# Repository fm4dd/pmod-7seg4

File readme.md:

## 7SEG4 PMOD

### Description

This PMOD provides a multiplexed four-digit 7-segment LED display output to FPGA designs via two double-row PMOD ports (quad-row).
The 7-segment display type "common anode" requires to use inverse logic. With inverse logic, setting the output "LOW" lights up the LED segment. Each digit has its own common anode, but the seven LED segments are shared. To display separate numbers on each digit, the program cycles through each anode with the apropriate segments enabled for this digit.

http://fpga.fm4dd.com/

### Schematic

### PCB Gerber
[7SEG4 PMOD Gerber V1.1](20200130-7seg4-gerber-v11.zip)

### Pin Assignments

#### IceBreaker v1.0

 J1# |  Label | Description   | PMOD1A
-----|--------|---------------|-------
1    |  A     | LED Segment A | 4
2    |  B     | LED Segment B | 2
3    |  C     | LED Segment C | 47
4    |  D     | LED Segment D | 45
7    |  E     | LED Segment E | 3
8    |  F     | LED Segment F | 48
9    |  G     | LED Segment G | 46
10   |  DP    | LED Segment DP| 44

 J2# |  Label | Description      | PMOD1B
-----|--------|------------------|-------
1    |  CA1   | Common AN Digit1 | 43
2    |  CA2   | Common AN Digit2 | 38
3    |  CA3   | Common AN Digit3 | 34
4    |  CA4   | Common AN Digit4 | 31
7    |  -     | Not connected    | 42
8    |  -     | Not connected    | 36
9    |  -     | Not connected    | 32
10   |  CA5   | Common AN Colon  | 28

#### DE0-Nano-SoC

The connection to Intels DE0-Nano-SoC is made through the pmod2nano adapter.

 J1# |  Label | Description    | GPIO0A | GPIO1A
-----|--------|----------------|--------|--------
1    |  E     |  LED Segment E | PIN_W12|PIN_AA15
2    |  F     |  LED Segment F | PIN_Y8 |PIN_AG26
3    |  G     |  LED Segment G | PIN_W8 |PIN_AF23
4    |  *     |  LED Segment DP| PIN_Y5 |PIN_AF21
7    |  A     |  LED Segment A | PIN_AF8|PIN_AH27
8    |  B     |  LED Segment B | PIN_AB4|PIN_AH24
9    |  C     |  LED Segment C | PIN_Y4 |PIN_AE22
10   |  D     |  LED Segment D | PIN_U11|PIN_AG20

 J2# |  Label | Description      | GPIO0B | GPIO1B
-----|--------|------------------|--------|--------
1    |  -     | Not connected    | PIN_AF4| PIN_AH23
2    |  -     | Not connected    | PIN_AF5| PIN_AE19
3    |  -     | Not connected    | PIN_T13| PIN_AD19
4    |  CA5   | Common AN DP     | PIN_AE7| PIN_AE24
7    |  CA1   | Common AN Digit1 | PIN_AG6| PIN_AG23
8    |  CA2   | Common AN Digit2 | PIN_AE4| PIN_AF18
9    |  CA3   | Common AN Digit3 | PIN_T11| PIN_AE20
10   |  CA4   | Common AN Digit4 | PIN_AF6| PIN_AD20

### Example

7SEG4 PMOD, connected to a Icebreaker v1.0 board

#### Verilog

Verilog test program pmod_7seg4_1.v (top-level):
```
// -------------------------------------------------------
// This program is a decimal counter 0..9999, displayed on
// the 4-digit 7-segment display. Counts in 1Hz intervals.
// 12MHz clock: set breakpoint at 23'd5999999 (icebreaker)
// 50MHz clock: set breakpoint at 25'd24999999 (de0-nano)
// -------------------------------------------------------
module pmod_7seg4_1 (
  input clk,
  output seg_a,
  output seg_b,
  output seg_c,
  output seg_d,
  output seg_e,
  output seg_f,
  output seg_g,
  output seg_dp,
  output ca1,
  output ca2,
  output ca3,
  output ca4
);

  reg clk_1hz = 1'b0;
  reg [22:0] clk_count = 23'd0;
  reg [3:0] DIGIT;
  reg [7:0] SEG;
  assign {seg_dp, seg_g, seg_f, seg_e, seg_d, seg_c, seg_b, seg_a} = SEG;
  assign {ca1, ca2, ca3, ca4} = DIGIT;
  reg [3:0] units, tens, hundreds, thousands;

  display_7seg display(.CLK (clk), .units (units), .tens (tens), .hundreds (hundreds), .thousands (thousands), .SEG (SEG), .DIGIT (DIGIT));

  always @(posedge clk)
  begin
    clk_count   <= clk_count + 1;
    if(clk_count == 23'd5999999)
    begin
      clk_count   <= 0;
      clk_1hz <= ~clk_1hz;
    end
  end

  always @(posedge clk_1hz)
  begin
    units <= units + 1;
    if (units == 9)
    begin
      units <= 0;
      tens <= tens + 1;
      if (tens == 9)
      begin
        tens <= 0;
        hundreds <= hundreds + 1;
        if (hundreds == 9)
        begin
          hundreds <= 0;
          thousands <= thousands + 1;
          if(thousands == 9)
          begin
            thousands <= 0;
          end
        end
      end
    end
  end
endmodule // end top-level module

// -------------------------------------------------------
// module display_7seg converts 4 decimal digits to 7-seg
// -------------------------------------------------------
module display_7seg(
  input CLK,
  input [3:0] units, tens, hundreds, thousands,
  output [7:0] SEG,
  output [3:0] DIGIT
);

  reg [3:0] digit_data;
  reg [1:0] digit_posn;
  reg [23:0] prescaler;

  encode_7seg encode(.CLK (CLK), .SEG (SEG), .D (digit_data));

  always @(posedge CLK)
  begin
    prescaler <= prescaler + 24'd1;
    if (prescaler == 24'd50000)     // set 1kHz multiplex frequency
    begin
      prescaler <= 0;               // reset the prescaler to zero
      digit_posn <= digit_posn + 2'd1;
      if (digit_posn == 0)
      begin
        digit_data <= units;       // assign digit_data
        DIGIT <= 4'b1110;          // set the 1 digit pin low (enable)
      end
      if (digit_posn == 2'd1)
      begin
        digit_data <= tens;        // assign digit_data to show tens
        DIGIT <= 4'b1101;          // set the 2 digit pin low (enable)
      end
      if (digit_posn == 2'd2)
      begin
        digit_data <= hundreds;    // assign digit_data to show hundreds
        DIGIT <= 4'b1011;          // set the 3 digit pin low (enable)
      end
      if (digit_posn == 2'd3)
      begin
        digit_data <= thousands;   // assign digit_data to show thousands
        DIGIT <= 4'b0111;          // set the 4 digit pin low (enable)
        digit_posn <= 0;           // reset position counter after 4nd digit
      end
    end
  end
endmodule

// -------------------------------------------------------
// module encode_7seg encodes a bin number as a 7seg digit
// -------------------------------------------------------
module encode_7seg(
  input CLK,
  input [3:0] D,
  output reg [7:0] SEG
);
  
  always @(posedge CLK)
    begin
      case(D)
        //              PGFEDCBA
        4'd0: SEG <= 8'b11000000;
        4'd1: SEG <= 8'b11111001;
        4'd2: SEG <= 8'b10100100;
        4'd3: SEG <= 8'b10110000;
        4'd4: SEG <= 8'b10011001;
        4'd5: SEG <= 8'b10010010;
        4'd6: SEG <= 8'b10000010;
        4'd7: SEG <= 8'b11111000;
        4'd8: SEG <= 8'b10000000;
        4'd9: SEG <= 8'b10010000;
        default: SEG <= 8'b11111111;
      endcase
    end
endmodule
```

#### VHDL

The Verilog example program pmod_7seg4_1.v converted to VHDL as pmod_7seg4_2.vhd:

```
-- -------------------------------------------------------
-- This program is a decimal counter 0..9999, displayed on
-- the 4-digit 7-segment display. Counts in 1Hz intervals.
-- -------------------------------------------------------
library ieee;
use ieee.std_logic_1164.all;
use ieee.numeric_std.all;

entity pmod_7seg4_2 is
port ( clk: in STD_LOGIC;
     seg_a: out STD_LOGIC := '1';
     seg_b: out STD_LOGIC := '1';
     seg_c: out STD_LOGIC := '1';
     seg_d: out STD_LOGIC := '1';
     seg_e: out STD_LOGIC := '1';
     seg_f: out STD_LOGIC := '1';
     seg_g: out STD_LOGIC := '1';
    seg_dp: out STD_LOGIC := '1';
       ca1: out STD_LOGIC := '1';
       ca2: out STD_LOGIC := '1';
       ca3: out STD_LOGIC := '1';
       ca4: out STD_LOGIC := '1'
);
end pmod_7seg4_2;

architecture arch of pmod_7seg4_2 is
  signal   clk_1hz: STD_LOGIC;
  signal     DIGIT: STD_LOGIC_VECTOR(3 downto 0);
  signal       SEG: STD_LOGIC_VECTOR(7 downto 0);
  signal unit, tens, hundreds, thousands: INTEGER range 0 to 9;

  -- -------------------------
  -- interface to display_7seg
  -- -------------------------
  component display_7seg is
  port ( CLK: IN  STD_LOGIC;
      unit, tens, hundreds, thousands: IN INTEGER := 0;  --digit values
     DIGIT:     OUT STD_LOGIC_VECTOR(3 DOWNTO 0);        --output digit number
                 SEG:   OUT STD_LOGIC_VECTOR(7 DOWNTO 0) --output segments
  );
  end component;

begin
  -- instantiation and value assignment to display_7seg
  display: display_7seg
  port map( clk, unit, tens, hundreds, thousands, DIGIT, SEG );

  counter_p: process( clk, clk_1hz, unit, tens, hundreds, thousands, DIGIT, SEG )
  variable clk_count: INTEGER := 0;

  begin
    if( rising_edge(clk) ) then
    clk_count := clk_count + 1;
      if( clk_count = 24999999 ) then
        clk_count := 0;
        clk_1hz <= NOT clk_1hz;
      end if;
    end if;

    if( rising_edge(clk_1hz) ) then
      unit <= unit + 1;
      if ( unit = 9 ) then
        unit <= 0;
        tens <= tens + 1;
        if ( tens = 9 ) then
          tens <= 0;
          hundreds <= hundreds + 1;
          if ( hundreds = 9 ) then
            hundreds <= 0;
            thousands <= thousands + 1;
            if( thousands = 9 ) then
              thousands <= 0;
            end if;
          end if;
        end if;
      end if;
    end if;
  end process counter_p;

  ca1 <= DIGIT(3);
  ca2 <= DIGIT(2);
  ca3 <= DIGIT(1);
  ca4 <= DIGIT(0);
  seg_a <= SEG(0);
  seg_b <= SEG(1);
  seg_c <= SEG(2);
  seg_d <= SEG(3);
  seg_e <= SEG(4);
  seg_f <= SEG(5);
  seg_g <= SEG(6);
  seg_dp <= SEG(7);
end arch;

-- -------------------------------------------------------
-- entity display_7seg converts 4 decimal digits to 7-seg
-- -------------------------------------------------------
library ieee;
use ieee.std_logic_1164.all;
use ieee.numeric_std.all;

entity display_7seg is
port ( CLK: IN  STD_LOGIC;
      unit: IN INTEGER;
      tens: IN INTEGER;
  hundreds: IN INTEGER;
 thousands: IN INTEGER;
     DIGIT: OUT STD_LOGIC_VECTOR(3 DOWNTO 0);  --output digit number
       SEG: OUT STD_LOGIC_VECTOR(7 DOWNTO 0)   --output segments
);
end display_7seg;

architecture arch of display_7seg is
  signal digit_data: INTEGER;
  -- ------------------------
  -- interface to encode_7seg
  -- ------------------------
  component encode_7seg is
  port( D: IN  INTEGER range 0 to 9;           --digit value input
      SEG: OUT STD_LOGIC_VECTOR(7 DOWNTO 0)    --output to segments
  );
  end component;

begin
  -- instantiation and value assignment to encode_7seg
  encode: encode_7seg port map( digit_data, SEG );

  display: process( clk )
  variable digit_posn: INTEGER range 0 to 3 := 0;
  variable  prescaler: INTEGER := 0;

  begin
  if( rising_edge(clk) ) then
    prescaler := prescaler + 1;
    if( prescaler = 50000 ) then -- 1ms refresh
      prescaler := 0;
      if (digit_posn = 0) then
        digit_data <= unit;      -- assign digit_data
        DIGIT <= "1110";         -- set the 1 digit pin low (enable)
      end if;
      if (digit_posn = 1) then
        digit_data <= tens;      -- assign digit_data to show tens
        DIGIT <= "1101";         -- set the 2 digit pin low (enable)
      end if;
      if (digit_posn = 2) then
        digit_data <= hundreds;  -- assign digit_data to show hundreds
        DIGIT <= "1011";         -- set the 3 digit pin low (enable)
      end if;
      if (digit_posn = 3) then
        digit_data <= thousands; -- assign digit_data to show thousands
        DIGIT <= "0111";         -- set the 4 digit pin low (enable)
      end if;
      digit_posn := digit_posn + 1;
    end if;
  end if;
  end process display;
end arch;

-- -------------------------------------------------------
-- entity encode_7seg encodes a bin number as a 7seg digit
-- -------------------------------------------------------
library ieee;
use ieee.std_logic_1164.all;
use ieee.numeric_std.all;

entity encode_7seg is
port (  D:      IN  INTEGER range 0 to 9;                 --digit value input
                SEG:    OUT STD_LOGIC_VECTOR(7 DOWNTO 0)  --output to segments
);
end encode_7seg;

architecture arch of encode_7seg is
begin
  with D select                       --map input D to segments
    SEG <= "11000000" WHEN 0,         --0
           "11111001" WHEN 1,         --1
           "10100100" WHEN 2,         --2
           "10110000" WHEN 3,         --3
           "10011001" WHEN 4,         --4
           "10010010" WHEN 5,         --5
           "10000010" WHEN 6,         --6
           "11111000" WHEN 7,         --7
           "10000000" WHEN 8,         --8
           "10010000" WHEN 9,         --9
           "11111111" WHEN OTHERS;    --default blank
end arch;
```

7SEG4 PMOD, connected to a DE0-Nano-SoC board

7SEG4 PMOD, connected to a 85K ULX3S board

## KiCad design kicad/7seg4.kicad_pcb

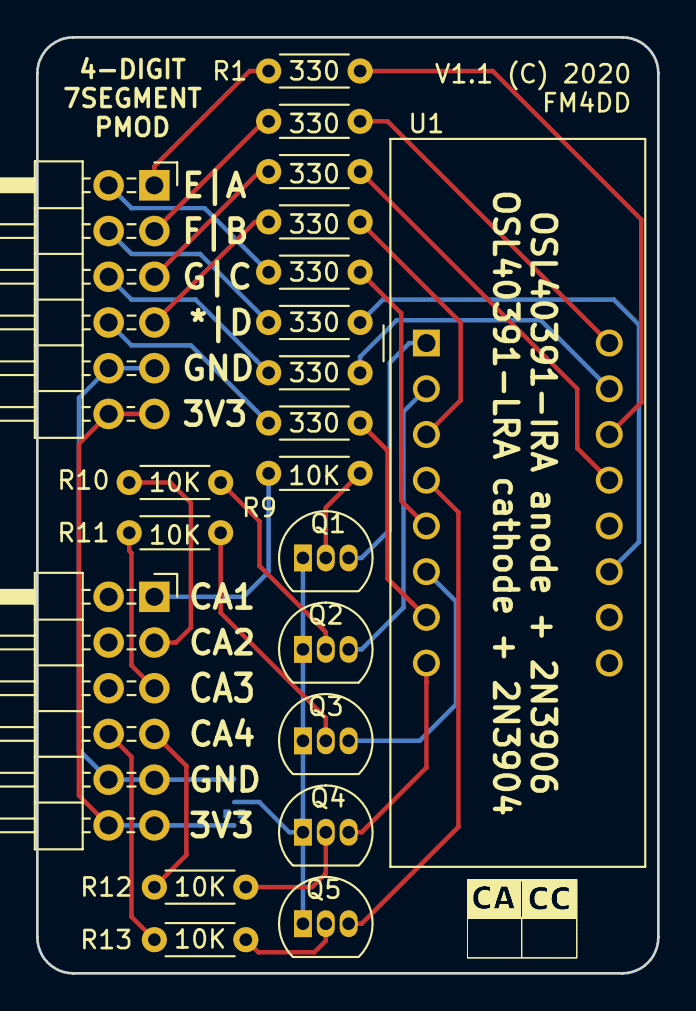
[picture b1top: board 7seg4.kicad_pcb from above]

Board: 2 copper layers, 34.5 x 52.0 mm, 23 parts (1 on the bottom side), 34 nets.

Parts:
7seg-type-display: 7seg-type-display
J1, J2: PMOD; PMODHeader_2x06_P2.54mm_Horizontal
JP1: common cathode selector; SolderJumper-3_P1.3mm_Bridged2Bar12_Pad1.0x1.5mm
Q1, Q2, Q3, Q4, Q5: 2N3906; TO-92_Inline
R1, R2, R3, R4, R5, R6, R7, R8: 330; R_Axial_DIN0204_L3.6mm_D1.6mm_P5.08mm_Horizontal
R9, R10, R11, R12, R13: 10K; R_Axial_DIN0204_L3.6mm_D1.6mm_P5.08mm_Horizontal
U1: 7SEG_OSL40391; 7SEG-OSL40391

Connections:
+3V3: J1.6, J1.12, J2.6, J2.12, JP1.1
/A: R1.2, U1.14
/AS: J1.1, R1.1
/B: R2.2, U1.16
/BS: J1.2, R2.1
/C: R3.2, U1.13
/CAP1: Q1.3, U1.1
/CAP2: Q2.3, U1.2
/CAP3: Q3.3, U1.6
/CAP4: Q4.3, U1.8
/CAP5: Q5.3, U1.4
/CAS1: J2.1, R9.1
/CAS2: J2.2, R10.1
/CAS3: J2.3, R11.1
/CAS4: J2.4, R12.1
/CAS5: J2.10, R13.1
/CS: J1.3, R3.1
/D: R4.2, U1.3
/DP: R8.2, U1.7
/DPS: J1.10, R8.1
/DS: J1.4, R4.1
/E: R5.2, U1.5
/ES: J1.7, R5.1
/F: R6.2, U1.11
/FS: J1.8, R6.1
/G: R7.2, U1.15
/GS: J1.9, R7.1
GND: J1.5, J1.11, J2.5, J2.11, JP1.3
unnamed: JP1.2, Q1.1, Q2.1, Q3.1, Q4.1, Q5.1
unnamed: Q1.2, R9.2
unnamed: Q2.2, R10.2
unnamed: Q3.2, R11.2
unnamed: Q4.2, R12.2
unnamed: Q5.2, R13.2

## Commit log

2020-03-20 add verilog example
2020-03-20 add fpga url
2020-04-04 fix pin assignment and add VHDL example
2020-04-04 mend
2020-04-19 add Verilog/VHDL demo code
2020-04-23 fix git lang discovery
2020-11-17 add ULX3S board example
2020-12-03 Add VHDL examples

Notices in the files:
kicad/7seg4.kicad_pcb:
License: CC-BY-SA 4.0
CC-BY-SA
V1.1 (C) 2020
